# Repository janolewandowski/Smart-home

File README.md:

# Smarthome
 Smarthome - PCB, STM32

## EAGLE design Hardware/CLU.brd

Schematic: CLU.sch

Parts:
BOOT0, BOOT1: SJ2W; SJ_2
BT1: VL-2320/HFN; BAT_VL-2320/HFN
C1, C2, C3, C4, C5, C6, C7, C8, C9, C11, C12, C13, C14, C17, C18, C19, C20, C21, C22, C23, C24, C25, C28, C31, C32: 100nF; C0805
C10: 0.022uF; C0805
C15: 470pF; C0805
C16: 1uF; C0805
C26, C27: 22pF; C0805
C29, C30: 100uF; SANYO-OSCON_SMD_E7
CAN_TERMINATOR: SJ
CRYSTAL1: LFSPXO025560; LFSPXO025560-SMD-4
D1: BYG10D; DIO_ES1J
ERROR: LEDCHIPLED_0805; CHIPLED_0805
EXT: PINHD-2X5; 2X05
F1: ERBRG1R25V; FUSC1206X75N
IC1: DS3231/SO; SO16W
IN_1, IN_2, IN_3, IN_4, IN_5, IN_6, IN_7, IN_8, IN_9, IN_10, IN_11: LEDCHIPLED_0805; CHIPLED_0805
J2: SI-60062-F; BEL_SI-60062-F
L1, L2, L3: L-USL2012C; L2012C
LS1: CEM-1205C; CUI_CEM-1205C
OK: LEDCHIPLED_0805; CHIPLED_0805
OUT1, OUT2, OUT3, OUT4, OUT5, OUT6, OUT7, OUT8, OUT9, OUT10: LEDCHIPLED_0805; CHIPLED_0805
PROG: PINHD-2X5; 2X05
Q1: CRYSTALHC49UP; HC49UP
R1, R2, R7, R8, R9, R10, R12, R13, R14, R15, R16, R17, R18, R19, R20, R21, R30, R31, R32, R33, R41, R42, R43, R44, R45, R46, R47, R48, R49, R60, R61, R62, R63: 10k; R0805
R3, R4: 330R; R0805
R5, R11: 120R; R0805
R6, R26: 4k7; R0805
R22, R23, R24, R25: 49R9; R0805
R27: 12.1k; R0805
R28, R29, R34, R50, R51, R52, R53, R54, R55, R56, R57, R58, R59, R64, R65, R66, R67, R68, R69, R70, R71, R72, R73, R74: 200R; R0805
R35, R36, R40, R75: 100R; R0805
R37: 1M; R0805
R38, R39: 1k5; R0805
RS_TERMINATOR: SJ
T1, T2, T3, T4, T5, T6, T7, T8, T9, T10, T11: BC848; SOT23
U1: AMS1117; SOT229P700X180-4N
U2: ST3485ECDR; SOIC127P600X175-8N
U3: STM32F107VCT6; QFP50P1600X1600X160-100N
U4: W25Q64BVSSIG; SOIC127P790X216-8N
U5: LAN8720A-CP; QFN50P400X400X100-25N
U6: 74LVC1G17W5-7; SOT95P280X145-5N
U7: SN65HVD230; SOIC127P599X175-8N
X1, X2: MKDSN1,5/10-5,08
X3: MKDSN1,5/2-5,08
X4: MKDSN1,5/5-5,08
X5, X6: MKDSN1,5/3-5,08

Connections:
12V: C3.1, C29.+, D1.K (CATHODE), F1.2, U1.3 (VIN)
BOOT0: BOOT0.2, U3.94 (BOOT0)
BUZZER: R33.1, U3.36 (PB1)
CAN_RX: U3.81 (PD0), U7.4 (R)
CAN_TX: U3.82 (PD1), U7.1 (D)
EHT_MDIO_LAN: R38.1, R75.2, U5.12 (MDIO)
ETH_CRS_DV: R40.1, U3.32 (PA7)
ETH_INT: R39.1, U3.15 (PC0), U5.14 (!NINT!/REFCLKO)
ETH_LED1: R28.1, U5.3 (LED1/REGOFF)
ETH_LED2: R29.1, U5.2 (LED2/!NINTSEL!)
ETH_MDC: U3.16 (PC1), U5.13 (MDC)
ETH_MDIO: R75.1, U3.25 (PA2)
ETH_RBIAS: R27.2, U5.24 (RBIAS)
ETH_RST: C9.1, R26.2, U5.15 (!NRST)
ETH_RXD0: R35.1, U3.33 (PC4)
ETH_RXD1: R36.1, U3.34 (PC5)
ETH_RX_N: C14.1, J2.6 (RD-), R25.2, U5.22 (RXN)
ETH_RX_P: C13.1, J2.4 (RD+), R24.2, U5.23 (RXP)
ETH_TXD0: U3.51 (PB12), U5.17 (TXD0)
ETH_TXD1: U3.52 (PB13), U5.18 (TXD1)
ETH_TX_EN: U3.48 (PB11), U5.16 (TXEN)
ETH_TX_N: C12.1, J2.3 (TD-), R23.2, U5.20 (TXN)
ETH_TX_P: C11.1, J2.1 (TD+), R22.2, U5.21 (TXP)
ETH_VDDA: C1.1, C2.1, J2.9 (YA), L1.2, L3.2, R22.1, R23.1, R24.1, R25.1, U5.1 (VDD2A), U5.19 (VDD1A)
ETH_VDDCR: C15.1, C16.1, U5.6 (VDDCR)
ETH_XTAL1: U3.24 (PA1), U5.5 (XTAL1/CLKLN), U6.4 (Y)
GND: BT1.N, C1.2, C2.2, C3.2, C4.2, C5.2, C6.2, C7.2, C8.2, C9.2, C10.2, C11.2, C12.2, C13.2, C14.2, C15.2, C16.2, C17.2, C18.2, C19.2, C20.2, C21.2, C22.2, C23.2, C24.2, C25.2, C26.1, C27.1, C28.2, C29.-, C30.-, C31.1, C32.2, CRYSTAL1.2 (GND), D1.A (ANODE), ERROR.C, EXT.7, IC1.5 (NC), IC1.6 (NC1), IC1.7 (NC2), IC1.8 (NC3), IC1.9 (NC4), IC1.10 (NC5), IC1.11 (NC6), IC1.12 (NC7), IC1.13 (GND), J2.8, J2.12 (GK), J2.S1 (SHIELD), J2.S2 (SHIELD), OK.C, PROG.4, R6.2, R27.1, R60.1, R61.1, T1.2 (E), T2.2 (E), T3.2 (E), T4.2 (E), T5.2 (E), T6.2 (E), T7.2 (E), T8.2 (E), T9.2 (E), T10.2 (E), T11.2 (E), U1.1 (ADJ/GND), U2.5 (GND), U3.10 (VSS), U3.19 (VSSA), U3.27 (VSS), U3.49 (VSS), U3.74 (VSS), U3.99 (VSS), U4.4 (GND), U5.25 (VSS), U6.3 (GND), U7.2 (GND), X2.7, X2.8, X3.1, X5.1, X6.3
I2C1_SCL: IC1.16 (SCL), R1.2, U3.92 (PB6), X2.10
I2C1_SDA: IC1.15 (SDA), R2.2, U3.93 (PB7), X2.9
IN_1: BOOT1.2, R44.2, R64.2, U3.37 (PB2), X4.1
IN_2: R30.2, R65.2, U3.38 (PE7), X4.2
IN_3: R31.2, R66.2, U3.39 (PE8), X4.3
IN_4: R43.2, R67.2, U3.40 (PE9), X4.4
IN_5: R41.2, R68.2, U3.41 (PE10), X4.5
IN_6: R45.2, R69.2, U3.42 (PE11), X2.1
IN_7: R42.2, R70.2, U3.43 (PE12), X2.2
IN_8: R46.2, R71.2, U3.44 (PE13), X2.3
IN_9: R48.2, R72.2, U3.45 (PE14), X2.4
IN_10: R47.2, R73.2, U3.46 (PE15), X2.5
IN_11: R49.2, R74.2, U3.47 (PB10), X2.6
LED_ERROR: R3.1, U3.3 (PE4)
LED_OK: R4.1, U3.2 (PE3)
unnamed: CAN_TERMINATOR.1, U7.7 (CANH), X5.2
unnamed: R11.2, U7.6 (CANL), X5.3
unnamed: R5.1, U2.6 (A), X6.1
unnamed: RS_TERMINATOR.2, U2.7 (B), X6.2
unnamed: BT1.P, IC1.14 (VBAT), R34.2
unnamed: R17.2, T6.1 (B)
unnamed: R18.2, T7.1 (B)
unnamed: R19.2, T8.1 (B)
unnamed: R20.2, T9.1 (B)
unnamed: OUT1.C, R50.1
unnamed: R21.2, T10.1 (B)
unnamed: R5.2, RS_TERMINATOR.1
unnamed: R6.1, U7.8 (RS)
unnamed: CAN_TERMINATOR.2, R11.1
unnamed: R12.2, T1.1 (B)
unnamed: R13.2, T2.1 (B)
unnamed: OK.A, R4.2
unnamed: ERROR.A, R3.2
unnamed: R14.2, T3.1 (B)
unnamed: R15.2, T4.1 (B)
unnamed: R16.2, T5.1 (B)
unnamed: OUT2.C, R51.1
unnamed: OUT3.C, R52.1
unnamed: OUT4.C, R53.1
unnamed: OUT5.C, R54.1
unnamed: C10.1, J2.2 (TCT), J2.5 (RCT), L3.1
unnamed: OUT6.C, R55.1
unnamed: OUT7.C, R56.1
unnamed: J2.11 (GA), R28.2
unnamed: J2.10 (YK), R29.2
unnamed: R36.2, U5.7 (RXD1/MODE1)
unnamed: R35.2, U5.8 (RXD0/MODE0)
unnamed: LS1.N, T11.3 (C)
unnamed: R33.2, T11.1 (B)
unnamed: OUT8.C, R57.1
unnamed: R40.2, U5.11 (CRS_DV/MODE2)
unnamed: OUT9.C, R58.1
unnamed: OUT10.C, R59.1
unnamed: IN_10.C, R73.1
unnamed: IN_1.C, R64.1
unnamed: BOOT1.1, R61.2
unnamed: BOOT0.1, R60.2
unnamed: BOOT0.3, R62.1
unnamed: BOOT1.3, R63.1
unnamed: IN_2.C, R65.1
unnamed: IN_3.C, R66.1
unnamed: IN_4.C, R67.1
unnamed: IN_5.C, R68.1
unnamed: IN_6.C, R69.1
unnamed: IN_7.C, R70.1
unnamed: IN_8.C, R71.1
unnamed: IN_9.C, R72.1
unnamed: IN_11.C, R74.1
OSC_IN: C26.2, Q1.2, R37.2, U3.12 (OSC_IN)
OSC_OUT: C27.2, Q1.1, R37.1, U3.13 (OSC_OUT)
POWER_IN: F1.1, X3.2
R1_S: R12.1, U3.88 (PD7)
R2_S: R13.1, U3.87 (PD6)
R3_S: R14.1, U3.86 (PD5)
R4_S: R15.1, U3.85 (PD4)
R5_S: R16.1, U3.84 (PD3)
R6_S: R17.1, U3.83 (PD2)
R7_S: R18.1, U3.80 (PC12)
R8_S: R19.1, U3.79 (PC11)
R9_S: R20.1, U3.78 (PC10)
R10_S: R21.1, U3.77 (PA15)
RST: C25.1, R32.1, U3.14 (NRST)
RTC_CHARGE: R34.1, U3.35 (PB0)
SPI1_EXCS: EXT.1, U3.95 (PB8)
SPI1_MISO: EXT.6, U3.90 (PB4), U4.2 (DO(IO1))
SPI1_MOSI: EXT.8, U3.91 (PB5), U4.5 (DI(IO0))
SPI1_SCK: EXT.10, U3.89 (PB3), U4.6 (CLK)
SWCLK: PROG.6, U3.76 (PA14)
SWDIO: PROG.2, U3.72 (PA13)
USART1_DE: R8.1, U2.3 (DE), U3.66 (PC9)
USART1_RE: R9.1, U2.2 (~RE), U3.67 (PA8)
USART1_RX: R10.1, U2.1 (RO), U3.69 (PA10)
USART1_TX: R7.1, U2.4 (DI), U3.68 (PA9)
USB_DM: EXT.2, U3.70 (PA11)
USB_DP: EXT.4, U3.71 (PA12)
VBAT: U3.6 (VBAT)
VCC: C4.1, C5.1, C6.1, C7.1, C8.1, C17.1, C18.1, C19.1, C20.1, C21.1, C22.1, C23.1, C24.1, C28.1, C30.+, C31.2, C32.1, CRYSTAL1.4 (VCC), EXT.3, IC1.2 (VCC), IN_1.A, IN_2.A, IN_3.A, IN_4.A, IN_5.A, IN_6.A, IN_7.A, IN_8.A, IN_9.A, IN_10.A, IN_11.A, L1.1, L2.1, L2.2, LS1.P, OUT1.A, OUT2.A, OUT3.A, OUT4.A, OUT5.A, OUT6.A, OUT7.A, OUT8.A, OUT9.A, OUT10.A, PROG.8, R1.1, R2.1, R7.2, R8.2, R9.2, R10.2, R26.1, R30.1, R31.1, R32.2, R38.2, R39.2, R41.1, R42.1, R43.1, R44.1, R45.1, R46.1, R47.1, R48.1, R49.1, R62.2, R63.2, U1.2 (VOUT), U1.4 (VOUT), U2.8 (VCC), U3.11 (VDD), U3.21 (VREF+), U3.22 (VDDA), U3.28 (VDD), U3.50 (VDD), U3.75 (VDD), U3.100 (VDD), U4.8 (VCC), U5.9 (VDDIO), U6.5 (VCC), U7.3 (VCC)
VREF-: U3.20 (VREF-)
W25Q64_CS: U3.54 (PB15), U4.1 (!CS)
W25Q64_HOLD: U3.56 (PD9), U4.7 (!HOLD!(IO3))
W25Q64_WP: U3.55 (PD8), U4.3 (!WP!(IO2))
X1: R50.2, T1.3 (C), X1.1
X2: R51.2, T2.3 (C), X1.2
X3: R52.2, T3.3 (C), X1.3
X4: R53.2, T4.3 (C), X1.4
X5: R54.2, T5.3 (C), X1.5
X6: R55.2, T6.3 (C), X1.6
X7: R56.2, T7.3 (C), X1.7
X8: R57.2, T8.3 (C), X1.8
X9: R58.2, T9.3 (C), X1.9
X10: R59.2, T10.3 (C), X1.10
X50_OUT: CRYSTAL1.3 (OUT), U6.2 (A)

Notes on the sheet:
RTC DS3231
LEDs
FLASH W25Q64
CAN MCP2551
RS485 ST3485
POWER
OUTPUT CONNECTOR
EXPANDER CONNECTOR
INPUT CONNECTOR
ETH LAN8720
ETH CONNECTOR
PULL - UP/DOWN
PROGRAMMING CONNECTOR
ETH_VDDIO

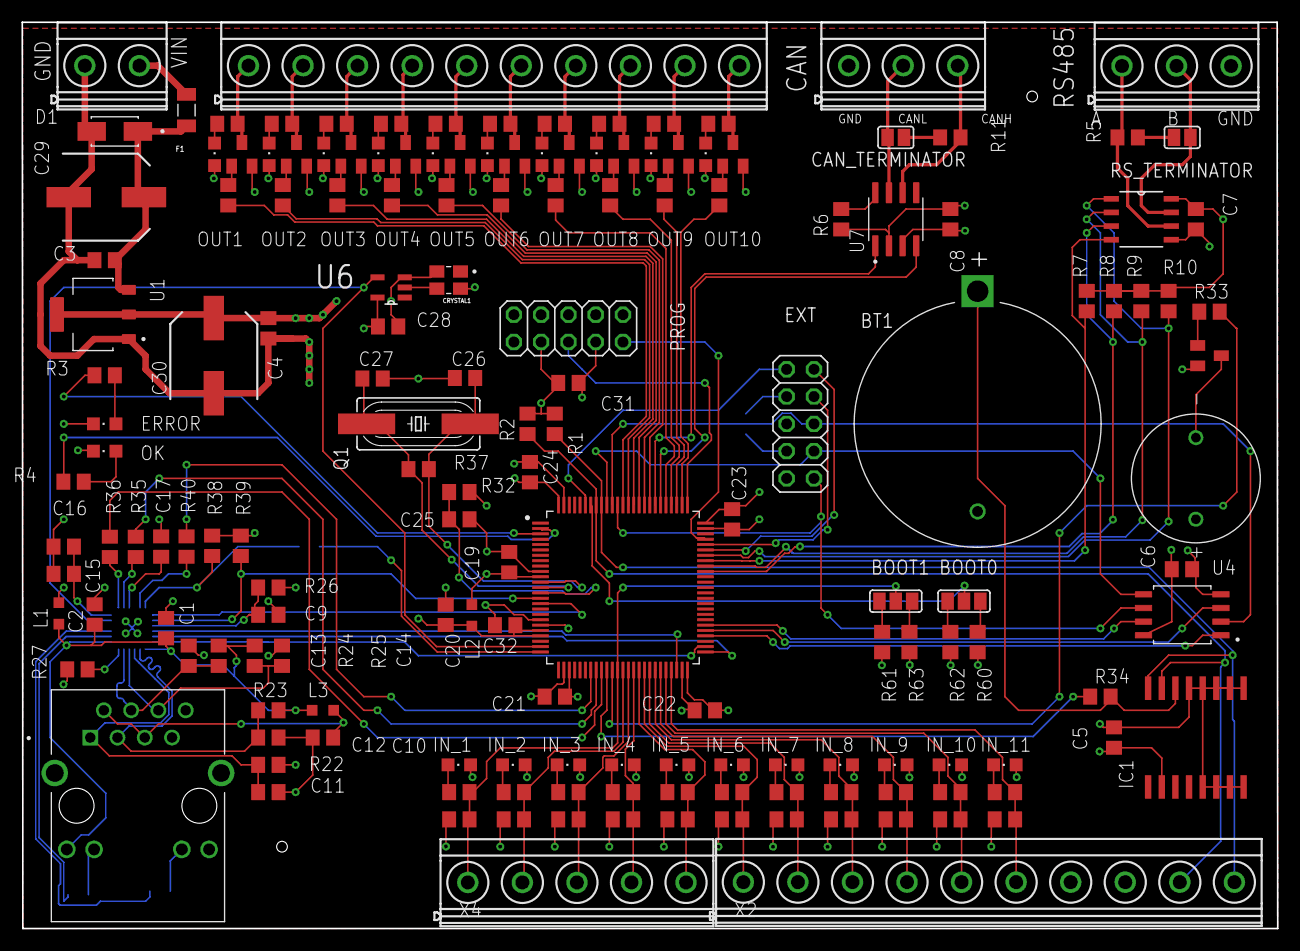
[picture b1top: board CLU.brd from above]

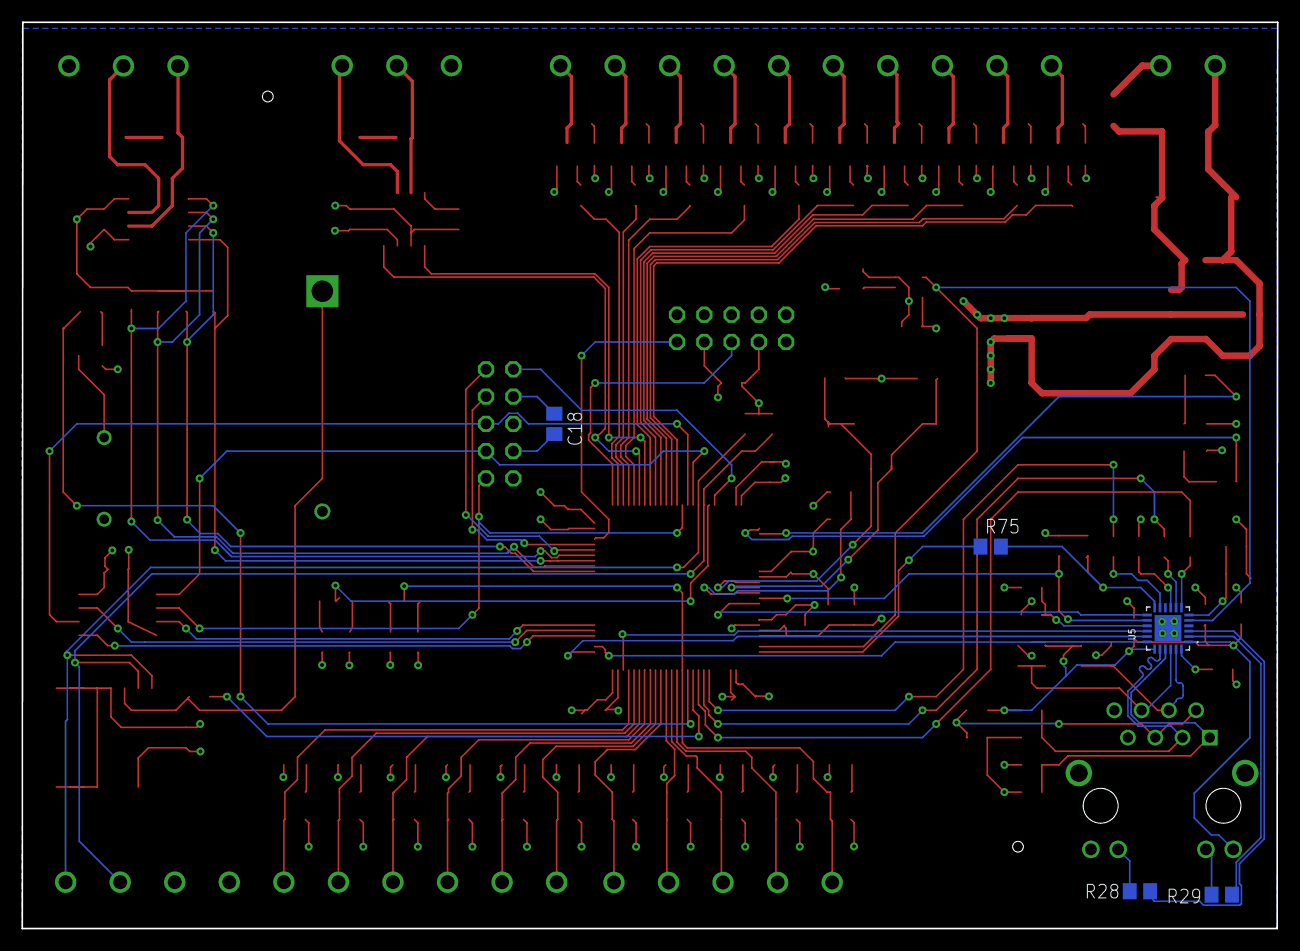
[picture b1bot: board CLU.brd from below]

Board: 4 copper layers, 116.9 x 84.4 mm, 171 parts (5 on the bottom side), 137 nets.

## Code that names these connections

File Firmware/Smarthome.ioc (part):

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Mcu.Name=STM32F107V(B-C)Tx
Mcu.Package=LQFP100
Mcu.UserName=STM32F107VCTx
PA1.Mode=RMII
PA1.Signal=ETH_REF_CLK
PA10.Mode=Asynchronous
PA10.Signal=USART1_RX
PA13.Mode=Serial_Wire
PA13.Signal=SYS_JTMS-SWDIO
PA14.Mode=Serial_Wire
PA14.Signal=SYS_JTCK-SWCLK
PA15.GPIOParameters=GPIO_Label
PA15.GPIO_Label=OUT_10
PA15.Signal=GPIO_Output
PA2.Mode=RMII
PA2.Signal=ETH_MDIO
PA7.Mode=RMII
PA7.Signal=ETH_CRS_DV
PA8.GPIOParameters=GPIO_Label
PA8.GPIO_Label=USART1_RE
PA8.Signal=GPIO_Output
PA9.Mode=Asynchronous
PA9.Signal=USART1_TX
PB0.GPIOParameters=GPIO_Label
PB0.GPIO_Label=RTC_CHARGE
PB0.Signal=GPIO_Output
PB1.GPIOParameters=GPIO_Label
PB1.GPIO_Label=BUZZER
PB1.Signal=GPIO_Output
PB10.GPIOParameters=GPIO_Label
PB10.GPIO_Label=IN_11
PB10.Signal=GPIO_Input
PB11.Mode=RMII
PB11.Signal=ETH_TX_EN
PB12.Mode=RMII
PB12.Signal=ETH_TXD0
PB13.Mode=RMII
PB13.Signal=ETH_TXD1
PB15.GPIOParameters=GPIO_Label
PB15.GPIO_Label=W25Q64_CS
PB15.Signal=GPIO_Output
PB2.GPIOParameters=GPIO_Label
PB2.GPIO_Label=IN_1
PB2.Signal=GPIO_Input
PB3.Mode=Full_Duplex_Master
PB3.Signal=SPI1_SCK
PB4.Mode=Full_Duplex_Master
PB4.Signal=SPI1_MISO
PB5.Mode=Full_Duplex_Master
PB5.Signal=SPI1_MOSI
PB6.Mode=I2C
PB6.Signal=I2C1_SCL
PB7.Mode=I2C
PB7.Signal=I2C1_SDA
PC0.GPIOParameters=GPIO_PuPd,GPIO_Label
PC0.GPIO_Label=ETH_INT
PC0.GPIO_PuPd=GPIO_NOPULL
PC0.Signal=GPIO_Input
PC1.Mode=RMII
PC1.Signal=ETH_MDC
PC10.GPIOParameters=GPIO_Label
PC10.GPIO_Label=OUT_9
PC10.Signal=GPIO_Output
PC11.GPIOParameters=GPIO_Label
PC11.GPIO_Label=OUT_8
PC11.Signal=GPIO_Output
PC12.GPIOParameters=GPIO_Label
PC12.GPIO_Label=OUT_7
PC12.Signal=GPIO_Output
PC4.Mode=RMII
PC4.Signal=ETH_RXD0
PC5.Mode=RMII
PC5.Signal=ETH_RXD1
PC9.GPIOParameters=GPIO_Label
PC9.GPIO_Label=USART1_DE
PC9.Signal=GPIO_Output
PD0.Mode=CAN_Activate
PD0.Signal=CAN1_RX
PD1.Mode=CAN_Activate
PD1.Signal=CAN1_TX
PD2.GPIOParameters=GPIO_Label
PD2.GPIO_Label=OUT_6
PD2.Signal=GPIO_Output
PD3.GPIOParameters=GPIO_Label
PD3.GPIO_Label=OUT_5
PD3.Signal=GPIO_Output
PD4.GPIOParameters=GPIO_Label
PD4.GPIO_Label=OUT_4
PD4.Signal=GPIO_Output
PD5.GPIOParameters=GPIO_Label
PD5.GPIO_Label=OUT_3
PD5.Signal=GPIO_Output
PD6.GPIOParameters=GPIO_Label
PD6.GPIO_Label=OUT_2
PD6.Signal=GPIO_Output
PD7.GPIOParameters=GPIO_Label
PD7.GPIO_Label=OUT_1
PD7.Signal=GPIO_Output
PD8.GPIOParameters=GPIO_Label
PD8.GPIO_Label=W25Q64_WP
PD8.Signal=GPIO_Output
PD9.GPIOParameters=GPIO_Label
PD9.GPIO_Label=W25Q64_HOLD
PD9.Signal=GPIO_Output
PE10.GPIOParameters=GPIO_Label
PE10.GPIO_Label=IN_5
PE10.Signal=GPIO_Input
PE11.GPIOParameters=GPIO_Label
PE11.GPIO_Label=IN_6
PE11.Signal=GPIO_Input
PE12.GPIOParameters=GPIO_Label
PE12.GPIO_Label=IN_7
PE12.Signal=GPIO_Input
PE13.GPIOParameters=GPIO_Label
PE13.GPIO_Label=IN_8
PE13.Signal=GPIO_Input
PE14.GPIOParameters=GPIO_Label
PE14.GPIO_Label=IN_9
PE14.Signal=GPIO_Input
PE15.GPIOParameters=GPIO_Label
PE15.GPIO_Label=IN_10
PE15.Signal=GPIO_Input
PE3.GPIOParameters=GPIO_Label
PE3.GPIO_Label=LED_ERROR
PE3.Signal=GPIO_Output
PE4.GPIOParameters=GPIO_Label
PE4.GPIO_Label=LED_OK
PE4.Signal=GPIO_Output
PE7.GPIOParameters=GPIO_Label
PE7.GPIO_Label=IN_2
PE7.Signal=GPIO_Input
PE8.GPIOParameters=GPIO_Label
PE8.GPIO_Label=IN_3
PE8.Signal=GPIO_Input
PE9.GPIOParameters=GPIO_Label
PE9.GPIO_Label=IN_4
PE9.Signal=GPIO_Input
RCC.SYSCLKFreq_VALUE=72000000
RCC.SYSCLKSource=RCC_SYSCLKSOURCE_PLLCLK
board=custom
